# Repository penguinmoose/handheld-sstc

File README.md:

# handheld-sstc
A handheld SSTC project on PCB, designed for a large magic wand form factor, entirely powered from 8s 18650. Uses direct secondary feedback with gate driver and MOSFETs, and 555 interrupter

Actual build changes that differ from PCB:
* R13 = 100k as-built (was 150k on pcb)
* R10 = 220ohm 2W instead of 150ohm 1/4W in order to prevent it from burning out
* C6 = some sort of 0603 0.1uf SMD capacitor extracted from an old PCB because I forgot to order it on DigiKey

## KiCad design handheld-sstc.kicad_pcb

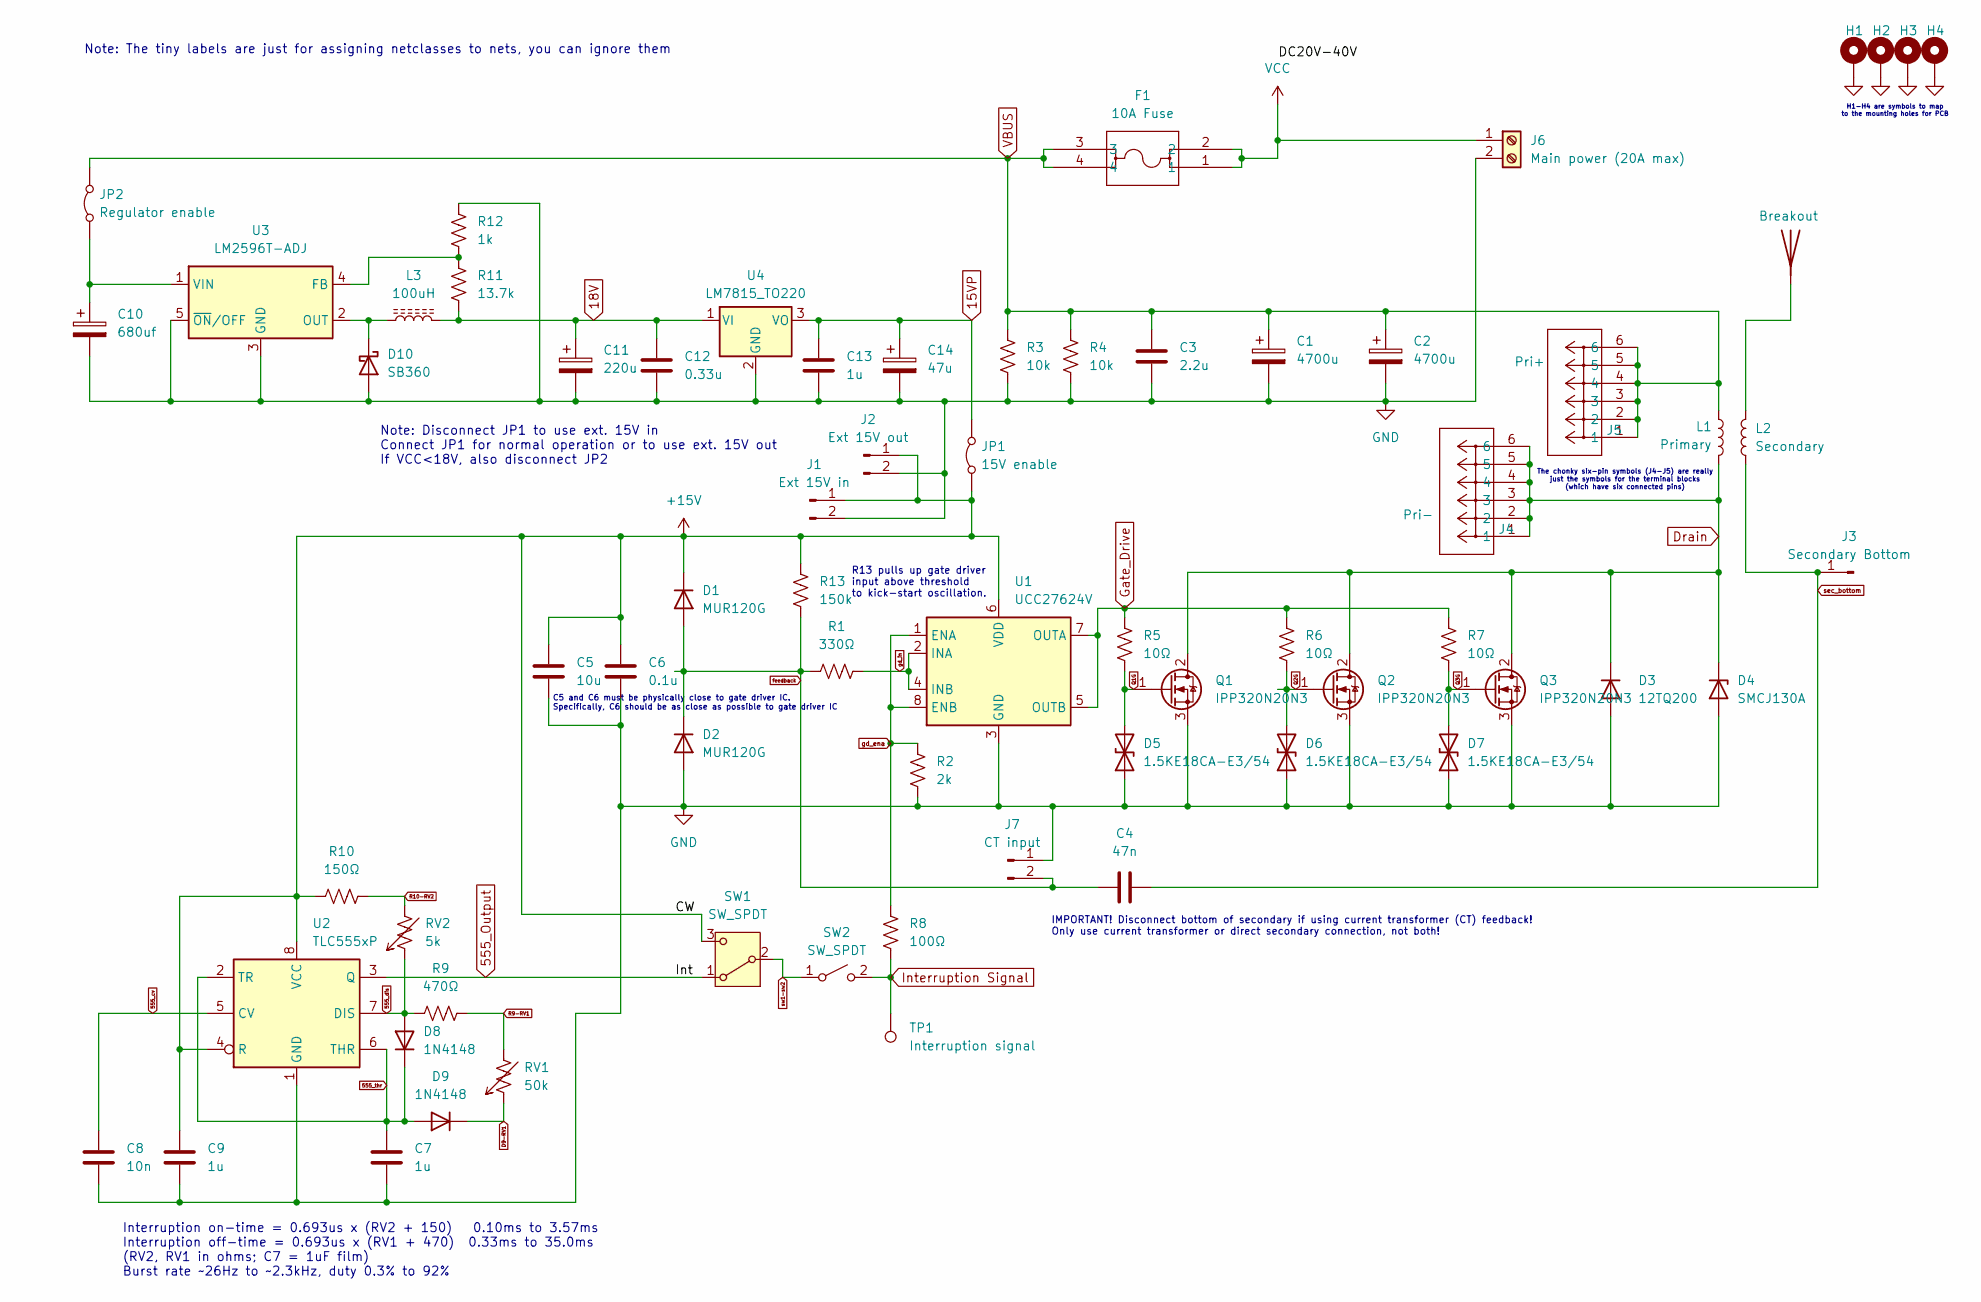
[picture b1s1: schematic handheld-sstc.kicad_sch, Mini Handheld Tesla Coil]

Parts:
C1, C2: 4700u; CP_Radial_D22.0mm_P10.00mm_SnapIn
C3: 2.2u; C_Rect_L26.5mm_W16mm_P22.50mm_MKS4
C4: 47n; C_Rect_L18.0mm_W9.0mm_P15.00mm_FKS3_FKP3
C5: 10u; R_1206_3216Metric_Pad1.30x1.75mm_HandSolder; Part CGA5L1X7R1H106K106AC
C6: 0.1u; C_0805_2012Metric_Pad1.18x1.45mm_HandSolder; Part C0805C104M5RACTU
C7: 1u; C_Rect_L7.2mm_W5.5mm_P5.00mm_FKS2_FKP2_MKS2_MKP2
C8: 10n; C_Disc_D5.0mm_W2.5mm_P5.00mm
C9, C13: 1u; C_Disc_D5.0mm_W2.5mm_P5.00mm
C10: 680uf; CP_Radial_D12.5mm_P5.00mm
C11: 220u; CP_Radial_D10.0mm_P5.00mm
C12: 0.33u; C_Disc_D5.0mm_W2.5mm_P5.00mm
C14: 47u; CP_Radial_D6.3mm_P2.50mm
D1, D2: MUR120G; D_DO-41_SOD81_P10.16mm_Horizontal
D3: 12TQ200; TO-220-2_Vertical
D4: SMCJ130A; D_SMC_Handsoldering
D5, D6, D7: 1.5KE18CA-E3/54; D_SMA-SMB_Universal_Handsoldering; Part SMBJ18CA
D8, D9: 1N4148; D_DO-35_SOD27_P7.62mm_Horizontal
D10: SB360; D_DO-201AD_P15.24mm_Horizontal
F1: 10A Fuse; 3522-2_KEY
H1, H2, H3, H4: MountingHole_Pad; MountingHole_4.3mm_M4_Pad_Via
J1: Ext 15V in; PinHeader_1x02_P2.54mm_Vertical
J2: Ext 15V out; JST_XH_B2B-XH-A_1x02_P2.50mm_Vertical
J3: Secondary Bottom; Conn_1x01_D1.00mm_LargeHandsolder
J4: Pri-; CONN_7799_KEY
J5: Pri+; CONN_7799_KEY
J6: Main power (20A max); TerminalBlock_Phoenix_MKDS-1,5-2-5.08_1x02_P5.08mm_Horizont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
J7: CT input; PinHeader_1x02_P2.54mm_Vertical
JP1: 15V enable; PinHeader_1x02_P2.54mm_Vertical
JP2: Regulator enable; PinHeader_1x02_P2.54mm_Vertical
L1: Primary
L2: Secondary
L3: 100uH; L_Toroid_Vertical_L16.0mm_W8.0mm_P7.62mm
Q1, Q2, Q3: IPP320N20N3; TO-220-3_Vertical
R1: 330Ω; R_0805_2012Metric_Pad1.20x1.40mm_HandSolder; Part AC0805FR-7W330RL
R2: 2k; R_Axial_DIN0207_L6.3mm_D2.5mm_P10.16mm_Horizontal
R3, R4: 10k; R_Axial_DIN0207_L6.3mm_D2.5mm_P10.16mm_Horizontal
R5, R6, R7: 10Ω; R_2512_6332Metric_Pad1.40x3.35mm_HandSolder; Part RMCF2512FT10R0
R8: 100Ω; R_Axial_DIN0207_L6.3mm_D2.5mm_P10.16mm_Horizontal
R9: 470Ω; R_Axial_DIN0207_L6.3mm_D2.5mm_P10.16mm_Horizontal
R10: 150Ω; R_Axial_DIN0207_L6.3mm_D2.5mm_P7.62mm_Horizontal
R11: 13.7k; R_Axial_DIN0207_L6.3mm_D2.5mm_P10.16mm_Horizontal
R12: 1k; R_Axial_DIN0207_L6.3mm_D2.5mm_P10.16mm_Horizontal
R13: 150k; R_Axial_DIN0207_L6.3mm_D2.5mm_P10.16mm_Horizontal
RV1: 50k; JST_XH_B2B-XH-A_1x02_P2.50mm_Vertical
RV2: 5k; JST_XH_B2B-XH-A_1x02_P2.50mm_Vertical
SW1: SW_SPDT; SW_Toggle_Copal_CF-LD-1DC6
SW2: SW_SPDT; JST_XH_B2B-XH-A_1x02_P2.50mm_Vertical
TP1: Interruption signal; TestPoint_THTPad_1.5x1.5mm_Drill0.7mm
U1: UCC27624V; SOIC-8_3.9x4.9mm_P1.27mm
U2: TLC555xP; DIP-8_W7.62mm_LongPads
U3: LM2596T-ADJ; TO-220-5_P3.4x3.7mm_StaggerOdd_Lead3.8mm_Vertical
U4: LM7815_TO220; TO-220-3_Vertical
~1: Breakout

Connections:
15VP: C13.1, C14.1, JP1.2 (B), U4.3 (VO)
18V: C11.1, C12.1, L3.2, R11.2, U4.1 (VI)
555_Output: SW1.1 (A), U2.3 (Q)
555_cv: C8.1, U2.5 (CV)
555_dis: D8.2 (A), R9.1, RV2.1, U2.7 (DIS)
555_thr: C7.1, D8.1 (K), D9.2 (A), U2.2 (TR), U2.6 (THR)
+15V: C5.1, C6.1, C9.1, D1.1 (K), J1.1, J2.1, JP1.1 (A), R10.1, R13.1, SW1.3 (C), U1.6 (VDD), U2.4 (R), U2.8 (VCC)
D9-RV1: D9.1 (K), RV1.1
Drain: D3.1 (K), D4.1 (K), J4.1, J4.2, J4.3, J4.4, J4.5, J4.6, L1.2, Q1.2 (D), Q2.2 (D), Q3.2 (D)
GND: C1.2, C2.2, C3.2, C5.2, C6.2, C7.2, C8.2, C9.2, C10.2, C11.2, C12.2, C13.2, C14.2, D2.2 (A), D3.2 (A), D4.2 (A), D5.1 (A1), D6.1 (A1), D7.1 (A1), D10.2 (A), H1.1, H2.1, H3.1, H4.1, J1.2, J2.2, J6.2, J7.1, Q1.3 (S), Q2.3 (S), Q3.3 (S), R2.2, R3.2, R4.2, R12.2, U1.3 (GND), U2.1 (GND), U3.3 (GND), U3.5 (~ON/OFF), U4.2 (GND)
Gate_Drive: R5.1, R6.1, R7.1, U1.5 (OUTB), U1.7 (OUTA)
Interruption Signal: R8.1, SW2.2 (B), TP1.1
unnamed: D10.1 (K), L3.1, U3.2 (OUT)
unnamed: C10.1, JP2.1 (A), U3.1 (VIN)
unnamed: L2.2, ~1.1
unnamed: R11.1, R12.1, U3.4 (FB)
Q1G: D5.2 (A2), Q1.1 (G), R5.2
Q2G: D6.2 (A2), Q2.1 (G), R6.2
Q3G: D7.2 (A2), Q3.1 (G), R7.2
R9-RV1: R9.2, RV1.2
R10-RV2: R10.2, RV2.2
VBUS: C1.1, C2.1, C3.1, F1.3, F1.4, J5.1, J5.2, J5.3, J5.4, J5.5, J5.6, JP2.2 (B), L1.1, R3.1, R4.1
VCC: F1.1, F1.2, J6.1
feedback: C4.1, D1.2 (A), D2.1 (K), J7.2, R1.1, R13.2
gd_ena: R2.1, R8.2, U1.1 (ENA), U1.8 (ENB)
gd_in: R1.2, U1.2 (INA), U1.4 (INB)
sec_bottom: C4.2, J3.1, L2.1
sw1-sw2: SW1.2 (B), SW2.1 (A)

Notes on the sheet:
The chonky six-pin symbols (J4-J5) are really just the symbols for the terminal blocks (which have six connected pins)
Interruption on-time = 0.693us x (RV2 + 150) 0.10ms to 3.57ms Interruption off-time = 0.693us x (RV1 + 470) 0.33ms to 35.0ms (RV2, RV1 in ohms; C7 = 1uF film) Burst rate ~26Hz to ~2.3kHz, duty 0.3% to 92%
Note: The tiny labels are just for assigning netclasses to nets, you can ignore them
R13 pulls up gate driver input above threshold to kick-start oscillation.
C5 and C6 must be physically close to gate driver IC. Specifically, C6 should be as close as possible to gate driver IC
IMPORTANT! Disconnect bottom of secondary if using current transformer (CT) feedback! Only use current transformer or direct secondary connection, not both!
Note: Disconnect JP1 to use ext. 15V in Connect JP1 for normal operation or to use ext. 15V out If VCC<18V, also disconnect JP2
H1-H4 are symbols to map to the mounting holes for PCB

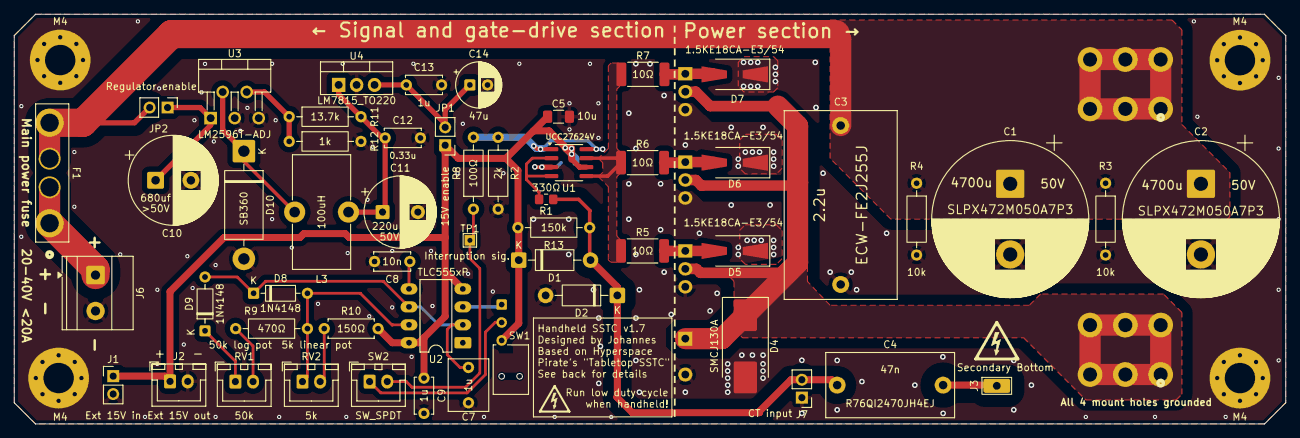
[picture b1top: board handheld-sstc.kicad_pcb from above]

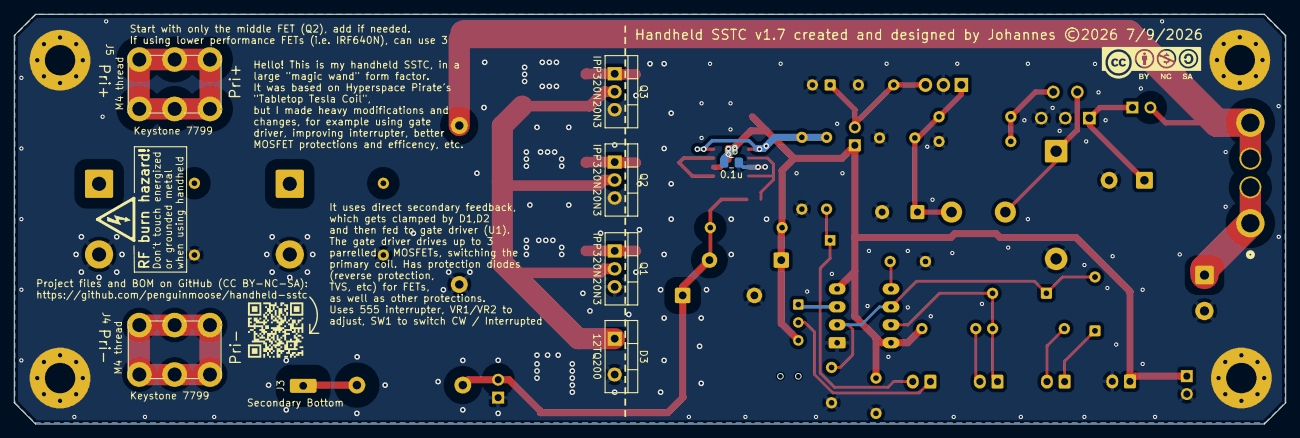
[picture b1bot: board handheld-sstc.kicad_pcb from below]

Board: 2 copper layers, 180.0 x 58.0 mm, 64 parts (7 on the bottom side), 27 nets.

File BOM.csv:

Part,Ref des,Value,Part number/description,Source,Qty,Price each,Total price,Notes
Main power capacitors,"C1,C2",4700uF,SLPX472M050A7P3,DigiKey,2,$3.81,$7.62,
Main power film capacitor,C3,2.2uF,ECW-FE2J225J,DigiKey,1,$1.88,$1.88,
Secondary drain feedback cap,C4,47nF,R76QI2470JH4EJ,Home,1,$1.01,$1.01,
Gate driver large decoupling capacitor,C5,10u,CGA5L1X7R1H106K160AC,DigiKey,1,$1.01,$1.01,Physically close to gate driver IC
Gate driver small decoupling capacitor,C6,0.1uF,C0805C104M5RACTU,Home,1,,,As close as physically possible to gate driver IC
555 timing capacitor,C7,1uf,R82DC4100AA60K,DigiKey,1,$0.60,$0.60,
555 CV pin noise filter capacitor,C8,10n,50V Ceramic capacitor,Home,1,,,
555 decoupling capacitor,C9,1u,50V Ceramic Capacitor,Home,1,,,
LM2596 input capacitor,C10,680uF,EKYC800ELL681MK30S,DigiKey,1,$1.86,$1.86,
LM2596 output capacitor,C11,220uF,50V Electrolytic Capacitor,Home,1,,,
LM7815 input bypass capacitor,C12,0.33u,50V Ceramic Capacitor,Home,1,,,
LM7815 output bypass capacitor,C13,1u,50V Ceramic Capacitor,Home,1,,,
LM7815 output bulk capacitor,C14,47u,50V Electrolytic Capacitor,Home,1,,,
Feedback voltage restricting diodes,"D1, D2",200V 1A,MUR120G,DigiKey,2,$0.59,$1.18,
Drain-source reverse protection diode,D3,200V 15A,12TQ200,DigiKey,1,$2.03,$2.03,
Drain-source unidirectional TVS diode,D4,130VWM 209VC,SMCJ130A,DigiKey,1,0.91,$0.91,
Gate reverse protection diodes,D5-D7,18V Bidir TVS,1.5KE18CA-E3/54,DigiKey,3,$1.41,$4.23,
555 oscillator diodes,"D8, D9",100 V 200mA,1N4148,Home,2,,,
LM2596 diode,D10,60V 3A Schkty,SB360-T,DigiKey,1,$0.98,$0.98,
Blade fuse fuseholder,F1,for 10A fuse,3522-2,DigiKey,1,$0.89,$0.89,For 10A fuse at power input
External 15V in,J1,-,Through hole PCB double,(On PCB),1,,,For external 15V in (instead of built in regulated 15V supply)
External 15V out,J2,-,Through hole PCB double,(On PCB),1,,,For external buck converter to fan
Secondary Bottom,J3,-,Through hole PCB single,(On PCB),1,,,
Primary PCB-end connection,"J4, J5",Screw terminal,Keystone 7799,DigiKey,2,$0.76,$1.52,
Main power in,J6,Screw terminal,EK508V-02P,DigiKey,1,$0.76,$0.76,
15V enable,JP1,-,Dupont male header x2,Home,1,,,
Regulator enable,JP2,-,Dupont male header x2,Home,1,,,
LM2596 inductor,L3,100uH,100uH 3A inductor,Home,1,,,
MOSFETs,Q1-Q3,Nch 200V 34A,IPP320N20N3,DigiKey,5,$3.36,$16.80,"On heatsink. Get more just in case they burn out, but really you only need one, or three if you need more current"
Gate driver input resistor,R1,330Ω (SMD),AC0805FR-7W330RL,DigiKey,1,$0.11,$0.11,Place physically close to gate driver
Enable pin pull down resistor,R2,2k,2kΩ 0.25W through-hole,Home,1,,,
Input capacitor discharge resistor,"R3, R4",10k,10k 0.25W through-hole,Home,1,,,
MOSFET gate input resistor,R5-R7,10Ω 1%1W SMD,RMCF2512FT10R0,DigiKey,3,$0.25,$0.75,
Gate driver input resistor,R8,100Ω,100Ω 0.25W through-hole,Home,1,,,
555 off-time fixed resistor,R9,470Ω 1% THT,MFR-25FRF52-470R,DigiKey,1,$0.10,$0.10,
555 on-time fixed resistor,R10,150Ω 1% THT,LR0204F150R,DigiKey,1,$0.10,$0.10,
LM2596 feedback voltage to output,R11,13.7k,MFR-25FBF52-13K7,DigiKey,1,$0.10,$0.10,
LM2596 feedback voltage to ground,R12,1k,1kΩ 0.25W 1% THT,Home,1,,,
Starting resistor to gate driver,R13,150k,MFR-25FRF52-150K,Home,1,,,Kick-starts oscillation by pulling up gate driver input
555 off-time adjustment potentiometer,RV1,50k log pot,PDB181-E420K-503A2,DigiKey,1,$1.77,$1.77,Uses JST-XH 1x02 connector on PCB
555 on-time adjustment potentiometer,RV2,5k linear pot,PDB181-K420K-502B,DigiKey,1,$1.63,$1.63,Uses JST-XH 1x02 connector on PCB
CW/Interrupted mode switch,SW1,SPDT THT,CF-LD-1DC6-AW2W,DigiKey,1,$2.12,$2.12,
On trigger button,SW2,12mm SPST-NO,PV5S24019,DigiKey,1,$5.59,$5.59,"Use JST-XH 1x02 connector on PCB, it is actually a JST-XH connector, but connect the 12mm button switch."
Gate Driver,U1,,UCC27624VDR,DigiKey,1,$1.26,$1.26,
555 Timer (for interruption),U2,,TLC555,Home,1,,,
VCC to 18V switching buck converter,U3,,LM2596TVADJG,DigiKey,1,$2.38,$2.38,
15V linear regulator,U4,,LM7815CT/NOPB,DigiKey,1,$1.86,$1.86,
Main Power Switch,Not PCB,SPST 16A 30V,RCA1913S1ABLKBLKWHT3,DigiKey,1,$3.96,$3.96,
Primary coil,Not PCB,10awg wire,,Home,1,,,
Primary wire-end connection,Not PCB,M4,3240027,DigiKey,2,$0.89,$1.78,From Phoenix Contact
Secondary coil,Not PCB,34awg wire,Red 34awg enameled wire,Amazon,1,$12.98,$12.98,Probably will only use around 1-2oz out of the 4oz
Secondary and body PVC tube,Not PCB,"2.5"" ID, 24"" length",,Other,,,,
JST XH socket leads,Not PCB,,ASXHSXH22K254,DigiKey,2,$0.81,$1.62,"There are two wires and two ends, so I can cut them in half to have 8x 5"" loose end leads for connecting JST-XH"
Total,,,,,,,$81.39,

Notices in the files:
handheld-sstc.kicad_pcb:
Handheld SSTC v1.7 created and designed by Johannes ©2026 7/9/2026
Project files and BOM on GitHub (CC BY-NC-SA):
https://github.com/penguinmoose/handheld-sstc
